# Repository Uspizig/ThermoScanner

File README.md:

# ThermoScanner: The Programmable Scanner for your K-Type Thermo Sensors with Display and Audio

## Features:

1. **AudioAmplifier MAX98357**: Listen to your favourite Tunes with an Audio Amplifier

2. **7 or 8 x K - Type Connectors** Perfect for measuring your heating system

3. **Max31855 or Max31856 Thermo Sensors** High precision

4. **I2C Connector for Sensor**: Connect your favourite I2C Sensor board with the embedded 2.54mm connector

5. **MicroSD Card**: Perfect for storing your thermo logger Data

6. **Wireless Control**: Untehther your development process with the wireless capabilities. With WiFi and BLE, this tool allows remote control and data logging. Users can adjust settings and monitor data from a distance, offering a more flexible development experience.

7. **Open Source & Programmable**: As an open-source device, the Device offers unmatched versatility. It is fully programmable, allowing you to tailor its functionality to your specific applications. This customization extends to software and hardware, opening up endless possibilities for creative and efficient project development.

8. **Compact Design**: Designed for convenience, the Thermologger Board compact and sleek form factor allows for seamless integration into existing setups. Its compatibility with USB PD sources and inline integration capability minimizes the need for additional equipment or extensive redesign, making it a versatile and user-friendly addition to any development environment.

9. **Display**: Monitor live the current status of all Thermo Logger sources or I2C Sensors

10. **Jog Dial** for operating the Device

9. **RGB LED**: Status LED
## Specifications

### Key Features:

### Future Developments:
1. Home Assistant integration

2. Eink Display for Power Saving

## Testing for Performance

At the heart of ThermoLogger's design is a commitment to reliability and performance. To ensure that SenseLoRaCam stands up to real-world demands, we subjected it to testing under use conditions.

## License

MIT License

Copyright (c) 2025 blue2monster

Permission is hereby granted, free of charge, to any person obtaining a copy
of this software and associated documentation files (the "Software"), to deal
in the Software without restriction, including without limitation the rights
to use, copy, modify, merge, publish, distribute, sublicense, and/or sell
copies of the Software, and to permit persons to whom the Software is
furnished to do so, subject to the following conditions:

The above copyright notice and this permission notice shall be included in all
copies or substantial portions of the Software.

THE SOFTWARE IS PROVIDED "AS IS", WITHOUT WARRANTY OF ANY KIND, EXPRESS OR
IMPLIED, INCLUDING BUT NOT LIMITED TO THE WARRANTIES OF MERCHANTABILITY,
FITNESS FOR A PARTICULAR PURPOSE AND NONINFRINGEMENT. IN NO EVENT SHALL THE
AUTHORS OR COPYRIGHT HOLDERS BE LIABLE FOR ANY CLAIM, DAMAGES OR OTHER
LIABILITY, WHETHER IN AN ACTION OF CONTRACT, TORT OR OTHERWISE, ARISING FROM,
OUT OF OR IN CONNECTION WITH THE SOFTWARE OR THE USE OR OTHER DEALINGS IN THE
SOFTWARE.

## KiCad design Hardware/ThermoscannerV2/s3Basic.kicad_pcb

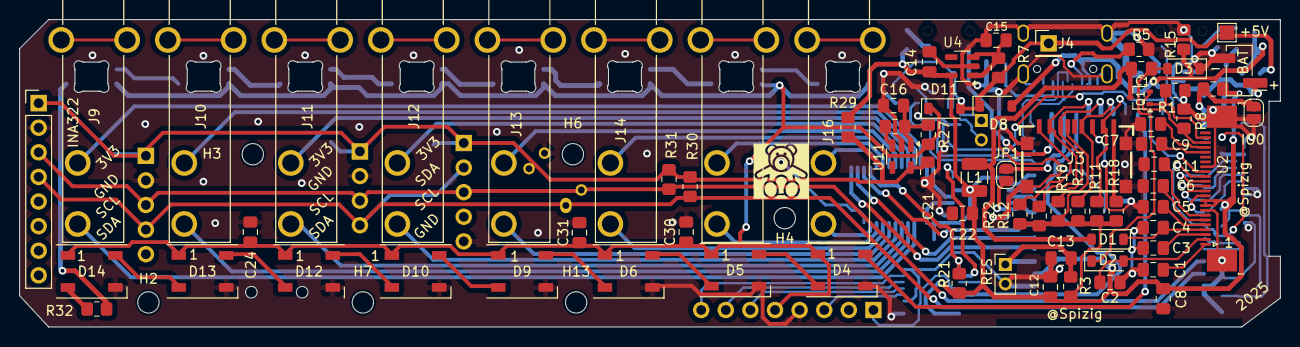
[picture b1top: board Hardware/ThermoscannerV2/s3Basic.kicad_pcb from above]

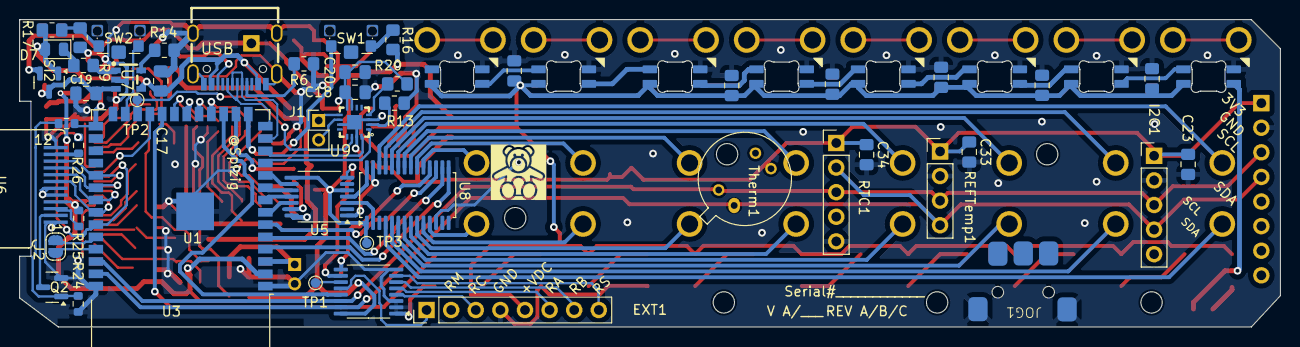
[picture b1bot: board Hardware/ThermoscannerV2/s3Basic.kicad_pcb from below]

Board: 2 copper layers, 130.2 x 31.7 mm, 140 parts (50 on the bottom side), 124 nets.

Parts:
+5V: TestPoint; TestPoint_Pad_1.5x1.5mm
BAT: PWR; PinHeader_1x02_P2.54mm_Vertical_SMD_Pin1Left
C1, C2, C3, C4, C5, C6, C7, C9, C11: 105; C_0805_2012Metric_Pad1.18x1.45mm_HandSolder
C8: 104; C_0805_2012Metric_Pad1.18x1.45mm_HandSolder
C10, C12, C14, C15, C16, C21: 4.7uF50V; C_0805_2012Metric_Pad1.18x1.45mm_HandSolder
C13, C17, C18, C19, C20, C22, C23, C24, C25, C26, C27, C28, C29, C30, C31, C32, C33, C34: 100nF; C_0805_2012Metric_Pad1.18x1.45mm_HandSolder
D1, D2, D3, D8, D11: MBR0530; D_SOD-123
D4, D5, D6, D9, D10, D12, D13, D14: WS2812B; LED_WS2812B_PLCC4_5.0x5.0mm_P3.2mm
D7: LED; LED_0805_2012Metric
D15, D16, D17, D18, D19, D20, D21, D22: SK6812MINI-E; MX_SK6812MINI-E
EXT1: Conn_01x08_Pin; PinHeader_1x08_P2.54mm_Vertical
H2, H3, H4, H6, H7, H13: MountingHole; MountingHole_2.2mm_M2
I2C1: Conn_01x05_Pin; PinHeader_1x05_P2.54mm_Vertical
INA322: Conn_01x08_Pin; PinHeader_1x08_P2.54mm_Vertical
IO0: Conn_01x02_Pin; SolderJumper-2_P1.3mm_Open_RoundedPad1.0x1.5mm
J1: Conn_01x02_Pin; PinHeader_1x02_P2.00mm_Vertical
J2: Conn_01x02_Pin; SolderJumper-2_P1.3mm_Open_RoundedPad1.0x1.5mm
J3: Micro_SD_Card_Det_US; TF-SMD_XKTF-0803-0
J4: Conn_01x01_Pin; PinHeader_1x01_P2.54mm_Vertical
J9, J10, J11, J12, J13, J14, J15, J16: PCC-SMP-V-K; OMEGA_PCC-SMP-V-K
JOG1: jogdial; JogWheel
JP1: SolderJumper_2_Open; SolderJumper-2_P1.3mm_Open_RoundedPad1.0x1.5mm
L1: 68uH1A; L_1210_3225Metric
LOG1, LOG2: MountingHole; baerklein
Q1: Si1308; SOT-323_SC-70
Q2: 2N7002; SOT-23
R1, R3, R4: 10K; R_0805_2012Metric_Pad1.20x1.40mm_HandSolder
R2, R10, R11, R12, R18, R21, R22, R30, R31: 10k; R_0805_2012Metric_Pad1.20x1.40mm_HandSolder
R5, R6: 5k11; R_0805_2012Metric_Pad1.20x1.40mm_HandSolder
R7, R27, R29, R32: 0R; R_0805_2012Metric_Pad1.20x1.40mm_HandSolder
R8: 3R; R_0805_2012Metric_Pad1.20x1.40mm_HandSolder
R9, R14: 1K; R_0805_2012Metric_Pad1.20x1.40mm_HandSolder
R13, R15, R16, R17, R28: 100K; R_0805_2012Metric_Pad1.20x1.40mm_HandSolder
R19: 300K; R_0805_2012Metric_Pad1.20x1.40mm_HandSolder
R20: 330k; R_0805_2012Metric_Pad1.20x1.40mm_HandSolder
R23: 10k; R_0603_1608Metric
R24: 1M; R_0603_1608Metric
R25: 22; R_0603_1608Metric
R26: 0R; R_0603_1608Metric
REFTemp1: Conn_01x04_Pin; PinHeader_1x04_P2.54mm_Vertical
RES: Conn_01x02_Pin; PinHeader_1x02_P2.00mm_Vertical
RTC1: Conn_01x05_Pin; PinHeader_1x05_P2.54mm_Vertical
SI2: SI2301CDS; SOT-23
SW1, SW2: SW_Push; SW_SPST_CK_KMS2xxGP
TP1, TP2, TP3: TestPoint; TestPoint_Pad_D1.0mm
Therm1: MLX90640
U1: ESP32-S3-WROOM-1-Espressif; ESP32-S3-WROOM-1
U2: FPCConn; TE_2-1734839-4_1x24-1MP_P0.5mm_Horizontal
U3: TCA9554PW; TSSOP-16_4.4x5mm_P0.65mm
U4, U11: RT9013; SOT-23-5
U5: MAX31856; TSSOP-14_4.4x5mm_P0.65mm
U6: GC9A01_IPS_display; GC9A01_IPS_display_reversed
U7: TP4065; SOT-23-5_L3.0-W1.7-P0.95-LS2.8-BR
U8: ADG1607xCP; TSSOP-28_4.4x9.7mm_P0.65mm
U9: TQFN-16_L3.0-W3.0-P0.50-BL-EP1.5
USB: KoreanHropartsElecTYPE-C-31-M-12; USB-C_SMD-TYPE-C-31-M-12

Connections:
+3.3VA: C21.2, C23.1, C33.1, C34.1, I2C1.1, INA322.1, R29.1, R30.2, R31.2, REFTemp1.1, RTC1.1, Therm1.2 (VDD), U11.5 (VOUT)
+3.3VP: C8.2, C12.2, C14.2, C22.2, J3.4 (VDD), L1.2, R2.1, R3.2, R4.2, R10.1, R11.2, R12.1, R16.1, R18.2, R21.2, R22.1, R25.2, R29.2, TP3.1, U1.2 (3V3), U2.9 (16), U2.10 (15), U3.16 (VDD), U4.5 (VOUT), U5.5 (AVDD), U5.8 (DVDD), U6.4 (VDD), U8.1 (V_{DD})
+4V: C24.1, C25.1, C26.1, C27.1, C28.1, C29.1, C30.1, C31.1, C32.1, D4.1 (VDD), D5.1 (VDD), D6.1 (VDD), D9.1 (VDD), D10.1 (VDD), D11.1 (K), D12.1 (VDD), D13.1 (VDD), D14.1 (VDD), D15.1 (VDD), D16.1 (VDD), D17.1 (VDD), D18.1 (VDD), D19.1 (VDD), D20.1 (VDD), D21.1 (VDD), D22.1 (VDD), EXT1.5, R27.2
+5V: C15.2, R7.1, U4.1 (VIN), U4.3 (EN)
+5VD: C17.1, D7.2 (A), D8.2 (A), R15.1, R17.1, SI2.1 (G), U7.4 (VCC), USB.A4 (VBUS), USB.A9 (VBUS), USB.B4 (VBUS), USB.B9 (VBUS)
+BATT: BAT.1, C19.2, SI2.3 (D), U7.3 (BAT)
/Audio_BCLK: U1.12 (GPIO8/TOUCH8/ADC1_CH7/SUBSPICS1), U9.16 (BCLK)
/Audio_DIN: U1.11 (GPIO18/U1RXD/ADC2_CH7/CLK_OUT3), U9.1 (DIN)
/Audio_LRC: TP2.1, U1.24 (GPIO47/SPICLK_P/SUBSPICLK_P_DIFF), U9.14 (LRCLK)
/BLK: IO0.1, R4.1, R23.2, U1.27 (GPIO0/BOOT)
/Button1: SW2.1, U1.25 (GPIO48/SPICLK_N/SUBSPICLK_N_DIFF)
/Button2: SW1.2, U1.15 (GPIO3/TOUCH3/ADC1_CH2)
/CMD: J3.3 (CMD), R10.2, U1.19 (GPIO11/TOUCH11/ADC2_CH0/FSPICS0/FSPIIO4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)
/D+: U1.14 (GPIO20/U1CTS/ADC2_CH9/CLK_OUT1/USB_D+), USB.A6 (DP1), USB.B6 (DP2)
/D-: U1.13 (GPIO19/U1RTS/ADC2_CH8/CLK_OUT2/USB_D-), USB.A7 (DN1), USB.B7 (DN2)
/DAT0: J3.7 (DAT0), R11.1, U1.21 (GPIO13/TOUCH13/ADC2_CH2/FSPIQ/FSPIIO7/S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)
/DAT1: J3.8 (DAT1), R18.1
/DAT3: J3.2 (DAT3/CD), R12.2, U1.18 (GPIO10/TOUCH10/ADC1_CH9/FSPICS0/FSPIIO4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)
/DIS_RES: R26.2, U1.35 (MTMS/GPIO42), U2.15 (10)
/EPD_BUSY: U1.23 (GPIO21), U2.16 (9)
/EPD_CLK: U1.33 (MTDO/GPIO40/CLK_OUT2), U2.12 (13), U6.8 (~CS)
/EPD_CS: U1.32 (MTCK/GPIO39/CLK_OUT3/SUBSPICS1), U2.13 (12), U6.9 (SCK)
/EPD_DC: U1.31 (GPIO38/FSPIWP/SUBSPIWP), U2.14 (11), U6.10 (SDI)
/EPD_MOSI: U1.34 (MTDI/GPIO41/CLK_OUT1), U2.11 (14), U6.7 (D/C)
/GPIO_INT: U1.17 (GPIO9/TOUCH9/ADC1_CH8/FSPIHD/SUBSPIHD), U3.13 (~INT)
/LEDK: Q2.3 (D), U6.2 (LEDK)
/ROT_A: EXT1.6, JOG1.1, U3.5 (P1)
/ROT_B: EXT1.7, JOG1.3, U3.6 (P2)
/ROT_C: EXT1.3, U3.4 (P0)
/ROT_L: EXT1.2, I2C1.5, TP1.1, U3.11 (P6)
/ROT_M: EXT1.1, U3.12 (P7)
/ROT_S: EXT1.8, JOG1.2, U3.7 (P3)
/RXD: J2.2, U1.36 (U0RXD/GPIO44/CLK_OUT2)
/SCL: I2C1.3, INA322.3, R31.1, REFTemp1.3, RTC1.3, Therm1.4 (SCL), U1.38 (GPIO2/TOUCH2/ADC1_CH1), U3.14 (SCL)
/SDA: I2C1.4, INA322.4, R30.1, REFTemp1.4, RTC1.2, Therm1.1 (SDA), U1.39 (GPIO1/TOUCH1/ADC1_CH0), U3.15 (SDA)
/SDCK: J3.5 (CLK), R2.2, U1.20 (GPIO12/TOUCH11/ADC2_CH0/FSPICS0/FSPIIO4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)
/SEL_R: Q1.2 (S), R8.2, U2.22 (3)
/T+: U5.4 (T+), U8.28 (DA)
/T+1: J16.P (POS), U8.19 (S1A)
/T+2: J15.P (POS), U8.20 (S2A)
/T+3: J14.P (POS), U8.21 (S3A)
/T+4: J13.P (POS), U8.22 (S4A)
/T+5: J12.P (POS), U8.23 (S5A)
/T+6: J11.P (POS), U8.24 (S6A)
/T+7: J10.P (POS), U8.25 (S7A)
/T+8: J9.P (POS), U8.26 (S8A)
/T-: U5.3 (T-), U8.2 (DB)
/T-1: J16.N (NEG), U8.11 (S1B)
/T-2: J15.N (NEG), U8.10 (S2B)
/T-3: J14.N (NEG), U8.9 (S3B)
/T-4: J13.N (NEG), U8.8 (S4B)
/T-5: J12.N (NEG), U8.7 (S5B)
/T-6: J11.N (NEG), U8.6 (S6B)
/T-7: J10.N (NEG), U8.5 (S7B)
/T-8: J9.N (NEG), U8.4 (S8B)
/TXD: J2.1, U1.37 (U0TXD/GPIO43/CLK_OUT1)
/Thermo_CS5: U1.10 (GPIO17/U1TXD/ADC2_CH6), U5.9 (~CS)
/Thermo_Enable: R21.1, U3.9 (P4), U8.18 (EN)
/Thermo_Fault: JP1.2 (B), U5.13 (~FAULT)
/Thermo_Matrix1: U1.6 (GPIO6/TOUCH6/ADC1_CH5), U8.17 (A0)
/Thermo_Matrix2: U1.5 (GPIO5/TOUCH5/ADC1_CH4), U8.16 (A1)
/Thermo_Matrix3: U1.4 (GPIO4/TOUCH4/ADC1_CH3), U8.15 (A2)
/Thermo_RDY: U3.10 (P5), U5.7 (~DRDY)
/Thermo_SCK: U1.9 (GPIO16/U0CTS/ADC2_CH5/XTAL_32K_NH5), U5.10 (SCK)
/Thermo_SI: U1.7 (GPIO7/TOUCH7/ADC1_CH6), U5.12 (SDI)
/Thermo_SO: U1.8 (GPIO15/U0RTS/ADC2_CH4/XTAL_32K_P), U5.11 (SDO)
/WS2812: D4.4 (DIN), U1.22 (GPIO14/TOUCH14/ADC2_CH3/FSPIWP/FSPIDQS/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)
/WS2812OUT: D14.2 (DOUT), R32.1
GND: BAT.2, C1.1, C2.1, C3.1, C4.1, C5.1, C6.1, C7.1, C8.1, C9.1, C11.1, C12.1, C13.1, C14.1, C15.1, C16.1, C17.2, C18.2, C19.1, C20.2, C21.1, C22.1, C23.2, C24.2, C25.2, C26.2, C27.2, C28.2, C29.2, C30.2, C31.2, C32.2, C33.2, C34.2, D3.1 (K), D4.3 (VSS), D5.3 (VSS), D6.3 (VSS), D9.3 (VSS), D10.3 (VSS), D12.3 (VSS), D13.3 (VSS), D14.3 (VSS), D15.3 (VSS), D16.3 (VSS), D17.3 (VSS), D18.3 (VSS), D19.3 (VSS), D20.3 (VSS), D21.3 (VSS), D22.3 (VSS), EXT1.4, I2C1.2, INA322.2, IO0.2, J3.6 (VSS), J3.10 (SHELL), J3.11 (SHELL), J3.12 (SHELL), J3.13 (SHELL), JOG1.4, Q2.2 (S), R1.2, R5.1, R6.1, R8.1, R13.1, R14.2, R15.2, R19.1, R24.1, REFTemp1.2, RES.2, RTC1.5, Therm1.3 (GND), U1.1 (GND), U1.40 (GND), U1.41 (GND), U2.8 (17), U2.17 (8), U2.MP (25), U3.1 (A0), U3.2 (A1), U3.3 (A2), U3.8 (GND), U4.2 (GND), U5.1 (AGND), U5.14 (DGND), U6.1 (GND), U6.5 (GND), U6.6 (GND), U6.12 (GND), U7.2 (GND), U8.12 (GND), U8.27 (V_{SS}), U9.3 (GND), U9.11 (GND), U9.15 (GND), U9.17 (GND), U11.2 (GND), USB.0, USB.A1 (GND), USB.A12 (GND), USB.B1 (GND), USB.B12 (GND)
unnamed: C10.1, D1.2 (A), L1.1, Q1.3 (D)
unnamed: C4.2, D1.1 (K), U2.4 (21)
unnamed: C2.2, D2.2 (A), U2.2 (23)
unnamed: C10.2, D2.1 (K), D3.2 (A)
unnamed: D4.2 (DOUT), D5.4 (DIN)
unnamed: D5.2 (DOUT), D6.4 (DIN)
unnamed: D6.2 (DOUT), D9.4 (DIN)
unnamed: D7.1 (K), R9.1
unnamed: D9.2 (DOUT), D10.4 (DIN)
unnamed: D10.2 (DOUT), D12.4 (DIN)
unnamed: D12.2 (DOUT), D13.4 (DIN)
unnamed: D13.2 (DOUT), D14.4 (DIN)
unnamed: D15.4 (DIN), R32.2
unnamed: D15.2 (DOUT), D16.4 (DIN)
unnamed: D16.2 (DOUT), D17.4 (DIN)
unnamed: D17.2 (DOUT), D18.4 (DIN)
unnamed: D18.2 (DOUT), D19.4 (DIN)
unnamed: D19.2 (DOUT), D20.4 (DIN)
unnamed: D20.2 (DOUT), D21.4 (DIN)
unnamed: D21.2 (DOUT), D22.4 (DIN)
unnamed: J1.1, U9.9 (OUTP)
unnamed: J1.2, U9.10 (OUTN)
unnamed: J3.1 (DAT2), R22.2
unnamed: J9.SH1 (SHIELD), J9.SH2 (SHIELD)
unnamed: J10.SH1 (SHIELD), J10.SH2 (SHIELD)
unnamed: J11.SH1 (SHIELD), J11.SH2 (SHIELD)
unnamed: J12.SH1 (SHIELD), J12.SH2 (SHIELD)
unnamed: J13.SH1 (SHIELD), J13.SH2 (SHIELD)
unnamed: J14.SH1 (SHIELD), J14.SH2 (SHIELD)
unnamed: J15.SH1 (SHIELD), J15.SH2 (SHIELD)
unnamed: J16.SH1 (SHIELD), J16.SH2 (SHIELD)
unnamed: JP1.1 (A), U1.16 (GPIO46)
unnamed: Q1.1 (G), R1.1, U2.23 (2)
unnamed: Q2.1 (G), R23.1, R24.2
unnamed: R16.2, SW1.1
unnamed: R17.2, R19.2, SW2.2
unnamed: C13.2, R3.1, RES.1, U1.3 (EN)
unnamed: C7.2, U2.21 (4)
unnamed: C9.2, U2.20 (5)
unnamed: C11.2, U2.7 (18)
unnamed: C6.2, U2.6 (19)
unnamed: C5.2, U2.5 (20)
unnamed: C3.2, U2.3 (22)
unnamed: C1.2, U2.1 (24)
unnamed: R25.1, U6.3 (LEDA)
unnamed: R26.1, U6.11 (~RESET)
unnamed: R9.2, U7.1 (CHRG)
unnamed: R14.1, U7.5 (PROG)
unnamed: R13.2, U9.2 (GAIN)
unnamed: R20.2, U9.4 (SD)
unnamed: R28.1, U11.3 (EN)
unnamed: C16.2, R27.1, R28.2, U11.1 (VIN)
unnamed: R6.2, USB.A5 (CC1)
unnamed: R5.2, USB.B5 (CC2)
VDC: +5V.1, C18.1, C20.1, D8.1 (K), D11.2 (A), J4.1, R7.2, R20.1, SI2.2 (S), U9.7 (VDD), U9.8 (VDD)

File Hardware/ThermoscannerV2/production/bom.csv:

Designator,Footprint,Quantity,Value,LCSC Part #
+5V,TestPoint_Pad_1.5x1.5mm,1,TestPoint,
BAT,PinHeader_1x02_P2.54mm_Vertical_SMD_Pin1Left,1,PWR,
"C1, C11, C2, C3, C4, C5, C6, C7, C9",0805,9,105,
"C10, C12, C14, C15, C16, C21",0805,6,4.7uF50V,
"C13, C17, C18, C19, C20, C22, C23, C24, C25, C26, C27, C28, C29, C30, C31, C32, C33, C34",0805,18,100nF,
C8,0805,1,104,
"D1, D11, D2, D3, D8",D_SOD-123,5,MBR0530,
"D10, D12, D13, D14, D4, D5, D6, D9",LED_WS2812B_PLCC4_5.0x5.0mm_P3.2mm,8,WS2812B,
"D15, D16, D17, D18, D19, D20, D21, D22",MX_SK6812MINI-E,8,SK6812MINI-E,
D7,0805,1,LED,
"EXT1, INA322",PinHeader_1x08_P2.54mm_Vertical,2,Conn_01x08_Pin,
"H13, H2, H3, H4, H6, H7",MountingHole_2.2mm_M2,6,MountingHole,
"I2C1, RTC1",PinHeader_1x05_P2.54mm_Vertical,2,Conn_01x05_Pin,
"IO0, J2",SolderJumper-2_P1.3mm_Open_RoundedPad1.0x1.5mm,2,Conn_01x02_Pin,
"J1, RES",PinHeader_1x02_P2.00mm_Vertical,2,Conn_01x02_Pin,
"J10, J11, J12, J13, J14, J15, J16, J9",OMEGA_PCC-SMP-V-K,8,PCC-SMP-V-K,
J3,TF-SMD_XKTF-0803-0,1,Micro_SD_Card_Det_US,
J4,PinHeader_1x01_P2.54mm_Vertical,1,Conn_01x01_Pin,
JOG1,JogWheel,1,jogdial,
L1,1210,1,68uH1A,
Q1,SOT-323_SC-70,1,Si1308,
Q2,SOT-23,1,2N7002,
"R1, R10, R11, R12, R18, R2, R21, R22, R3, R30, R31, R4",0805,12,10K,
"R13, R15, R16, R17, R28",0805,5,100K,
"R14, R9",0805,2,1K,
R19,0805,1,300K,
R20,0805,1,330k,
R23,0603,1,10k,
R24,0603,1,1M,
R25,0603,1,22,
R26,0603,1,0R,
"R27, R29, R32, R7",0805,4,0R,
"R5, R6",0805,2,5k11,
R8,0805,1,3R,
REFTemp1,PinHeader_1x04_P2.54mm_Vertical,1,Conn_01x04_Pin,
SI2,SOT-23,1,SI2301CDS,
"SW1, SW2",SW_SPST_CK_KMS2xxGP,2,SW_Push,
"TP1, TP2, TP3",TestPoint_Pad_D1.0mm,3,TestPoint,
Therm1,MLX90640,1,MLX90640,
U1,ESP32-S3-WROOM-1,1,ESP32-S3-WROOM-1-Espressif,
"U11, U4",SOT-23-5,2,RT9013,
U2,TE_2-1734839-4_1x24-1MP_P0.5mm_Horizontal,1,FPCConn,
U3,TSSOP-16_4.4x5mm_P0.65mm,1,TCA9554PW,
U5,TSSOP-14_4.4x5mm_P0.65mm,1,MAX31856,
U6,GC9A01_IPS_display_reversed,1,GC9A01_IPS_display,
U7,SOT-23-5_L3.0-W1.7-P0.95-LS2.8-BR,1,TP4065,
U8,TSSOP-28_4.4x9.7mm_P0.65mm,1,ADG1607xCP,
U9,TQFN-16_L3.0-W3.0-P0.50-BL-EP1.5,1,~,
USB,USB-C_SMD-TYPE-C-31-M-12,1,KoreanHropartsElecTYPE-C-31-M-12,

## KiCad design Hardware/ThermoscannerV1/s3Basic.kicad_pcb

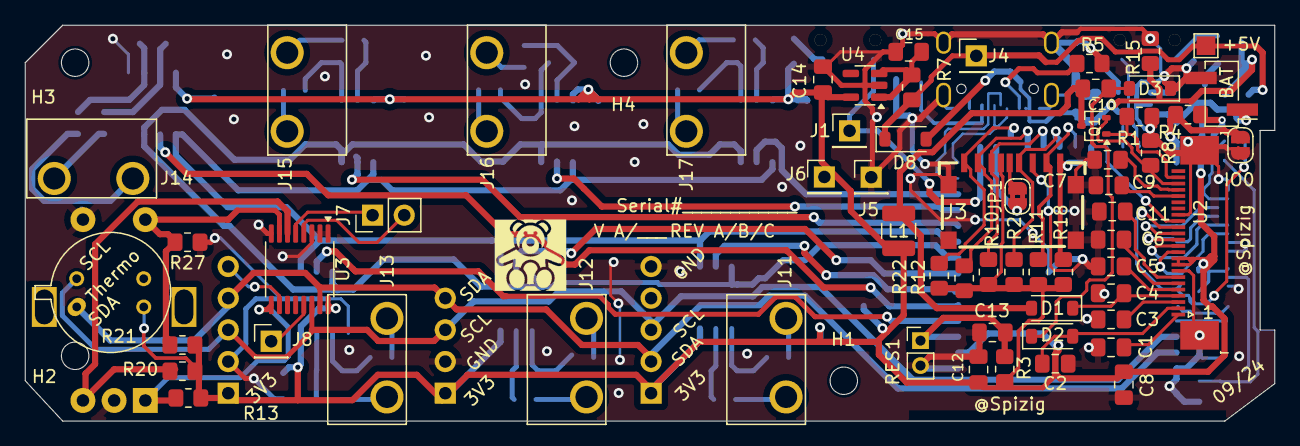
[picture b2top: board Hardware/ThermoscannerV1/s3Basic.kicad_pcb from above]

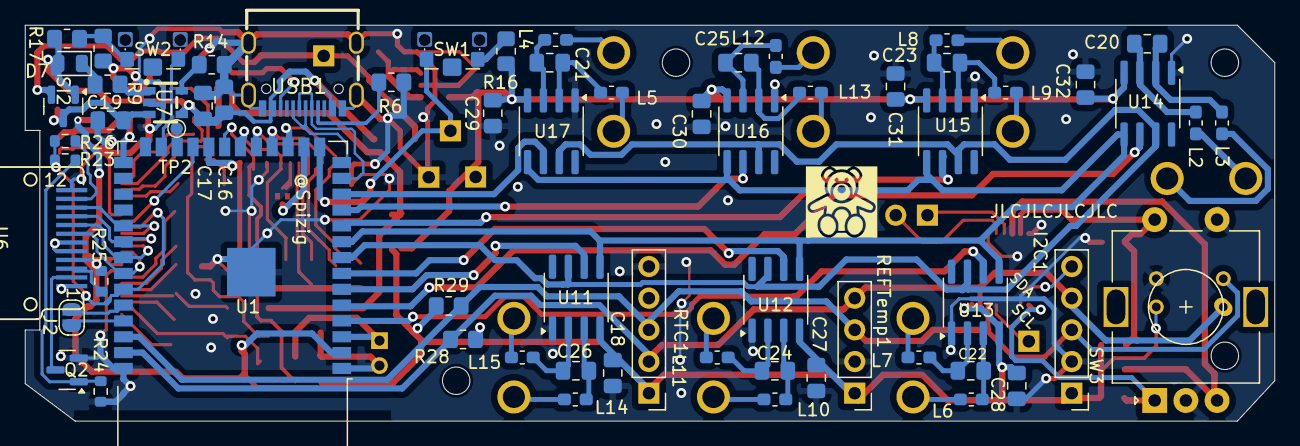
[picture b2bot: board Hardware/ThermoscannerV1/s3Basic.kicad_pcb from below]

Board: 2 copper layers, 100.2 x 31.7 mm, 132 parts (66 on the bottom side), 99 nets.

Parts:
+5V: TestPoint; TestPoint_Pad_1.5x1.5mm
BAT: PWR; PinHeader_1x02_P2.54mm_Vertical_SMD_Pin1Left
C1, C2, C3, C4, C5, C6, C7, C9, C11: 105; C_0805_2012Metric_Pad1.18x1.45mm_HandSolder
C8: 104; C_0805_2012Metric_Pad1.18x1.45mm_HandSolder
C10, C12, C14, C15: 4.7uF50V; C_0805_2012Metric_Pad1.18x1.45mm_HandSolder
C13, C17, C18, C19, C20, C21, C22, C23, C24, C25, C26, C27, C28, C29, C30, C31, C32: 100nF; C_0805_2012Metric_Pad1.18x1.45mm_HandSolder
C16: 1uF; C_0805_2012Metric_Pad1.18x1.45mm_HandSolder
D1, D2, D3, D8: MBR0530; D_SOD-123
D7: LED; LED_0805_2012Metric
H1, H2, H3, H4: MountingHole; MountingHole_2.2mm_M2
I2C1: Conn_01x05_Pin; PinHeader_1x05_P2.54mm_Vertical
IO0: Conn_01x02_Pin; SolderJumper-2_P1.3mm_Open_RoundedPad1.0x1.5mm
J1, J4, J5, J6, J8: Conn_01x01_Pin; PinHeader_1x01_P2.54mm_Vertical
J2: Conn_01x02_Pin; SolderJumper-2_P1.3mm_Open_RoundedPad1.0x1.5mm
J3: Micro_SD_Card_Det_US; TF-SMD_XKTF-0803-0
J7: Conn_01x02_Pin; PinHeader_1x02_P2.54mm_Vertical
J11, J12, J13, J14, J15, J16, J17: PCC-SMP-V-K; OMEGA_PCC-SMP-V-K
JP1: Jumper_2_Open; SolderJumper-2_P1.3mm_Bridged2Bar_RoundedPad1.0x1.5mm
L1: 68uH1A; L_1210_3225Metric
L2, L3, L4, L5, L6, L7, L8, L9, L10, L11, L12, L13, L14, L15: L; L_0603_1608Metric_Pad1.05x0.95mm_HandSolder
LOG1, LOG2: MountingHole; baerklein
Q1: Si1308; SOT-323_SC-70
Q2: 2N7002; SOT-23
R1, R3, R4: 10K; R_0805_2012Metric_Pad1.20x1.40mm_HandSolder
R2, R10, R11, R12, R13, R18, R20, R21, R22, R27, R28, R29: 10k; R_0805_2012Metric_Pad1.20x1.40mm_HandSolder
R5, R6: 5k11; R_0805_2012Metric_Pad1.20x1.40mm_HandSolder
R7: 0R; R_0805_2012Metric_Pad1.20x1.40mm_HandSolder
R8: 3R; R_0805_2012Metric_Pad1.20x1.40mm_HandSolder
R9, R14: 1K; R_0805_2012Metric_Pad1.20x1.40mm_HandSolder
R15, R16, R17: 100K; R_0805_2012Metric_Pad1.20x1.40mm_HandSolder
R19: 300K; R_0805_2012Metric_Pad1.20x1.40mm_HandSolder
R23: 10k; R_0603_1608Metric
R24: 1M; R_0603_1608Metric
R25: 22; R_0603_1608Metric
R26: 0R; R_0603_1608Metric
REFTemp1: Conn_01x04_Pin; PinHeader_1x04_P2.54mm_Vertical
RES1: Conn_01x02_Pin; PinHeader_1x02_P2.00mm_Vertical
RTC1: Conn_01x05_Pin; PinHeader_1x05_P2.54mm_Vertical
SI2: SI2301CDS; SOT-23
SW1, SW2: SW_Push; SW_SPST_CK_KMS2xxGP
SW3: Rotary_Encoder_Switch; RotaryEncoder_Alps_EC11E-Switch_Vertical_H20mm
TP2: TestPoint; TestPoint_Pad_D1.0mm
Thermo: MLX90640
U1: ESP32-S3-WROOM-1-Espressif; ESP32-S3-WROOM-1
U2: FPCConn; TE_2-1734839-4_1x24-1MP_P0.5mm_Horizontal
U3: TCA9554PW; TSSOP-16_4.4x5mm_P0.65mm
U4: RT9013; SOT-23-5
U6: GC9A01_IPS_display; GC9A01_IPS_display_reversed
U7: TP4065; SOT-23-5_L3.0-W1.7-P0.95-LS2.8-BR
U11, U12, U13, U14, U15, U16, U17: MAX31855KASA; SOIC-8_3.9x4.9mm_P1.27mm
USB1: KoreanHropartsElecTYPE-C-31-M-12; USB-C_SMD-TYPE-C-31-M-12

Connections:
+3.3VP: C8.2, C12.2, C14.2, C18.2, C27.2, C28.2, C29.2, C30.2, C31.2, C32.2, I2C1.1, J3.4 (VDD), J6.1, L1.2, R2.1, R3.2, R4.2, R10.1, R11.2, R12.1, R13.1, R16.1, R18.2, R20.2, R21.2, R22.1, R25.2, R28.2, R29.2, REFTemp1.1, RTC1.1, Thermo.2 (VDD), U1.2 (3V3), U2.9 (16), U2.10 (15), U3.16 (VDD), U4.5 (VOUT), U6.4 (VDD), U11.4 (V_CC), U12.4 (V_CC), U13.4 (V_CC), U14.4 (V_CC), U15.4 (V_CC), U16.4 (V_CC), U17.4 (V_CC)
+5V: C15.2, R7.1, U4.1 (VIN), U4.3 (EN)
+5VD: C16.1, C17.1, D7.2 (A), D8.2 (A), R15.1, R17.1, SI2.1 (G), U7.4 (VCC), USB1.A4 (VBUS), USB1.A9 (VBUS), USB1.B4 (VBUS), USB1.B9 (VBUS)
+BATT: BAT.1, C19.2, SI2.3 (D), U7.3 (BAT)
/BLK: R23.2, R26.2, U1.35 (MTMS/GPIO42), U2.15 (10)
/Button1: SW2.1, U1.25 (GPIO48/SPICLK_N/SUBSPICLK_N_DIFF)
/Button2: J1.1, SW1.2, U1.15 (GPIO3/TOUCH3/ADC1_CH2)
/CMD: J3.3 (CMD), R10.2, U1.19 (GPIO11/TOUCH11/ADC2_CH0/FSPICS0/FSPIIO4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)
/D+: U1.14 (GPIO20/U1CTS/ADC2_CH9/CLK_OUT1/USB_D+), USB1.A6 (DP1), USB1.B6 (DP2)
/D-: U1.13 (GPIO19/U1RTS/ADC2_CH8/CLK_OUT2/USB_D-), USB1.A7 (DN1), USB1.B7 (DN2)
/DAT0: J3.7 (DAT0), R11.1, U1.21 (GPIO13/TOUCH13/ADC2_CH2/FSPIQ/FSPIIO7/S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)
/DAT1: J3.8 (DAT1), R18.1, U1.22 (GPIO14/TOUCH14/ADC2_CH3/FSPIWP/FSPIDQS/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)
/DAT2: J3.1 (DAT2), R22.2, U1.17 (GPIO9/TOUCH9/ADC1_CH8/FSPIHD/SUBSPIHD)
/DAT3: J3.2 (DAT3/CD), R12.2, U1.18 (GPIO10/TOUCH10/ADC1_CH9/FSPICS0/FSPIIO4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)
/EPD_BUSY: U1.23 (GPIO21), U2.16 (9)
/EPD_CLK: U1.33 (MTDO/GPIO40/CLK_OUT2), U2.12 (13), U6.8 (~CS)
/EPD_CS: U1.32 (MTCK/GPIO39/CLK_OUT3/SUBSPICS1), U2.13 (12), U6.9 (SCK)
/EPD_DC: U1.31 (GPIO38/FSPIWP/SUBSPIWP), U2.14 (11), U6.10 (SDI)
/EPD_MOSI: U1.34 (MTDI/GPIO41/CLK_OUT1), U2.11 (14), U6.7 (D/C)
/IO0: IO0.1, R4.1, U1.27 (GPIO0/BOOT)
/LEDK: Q2.3 (D), U6.2 (LEDK)
/ROT_A: R13.2, SW3.A, U3.9 (P4)
/ROT_B: R20.1, SW3.B, U3.6 (P2)
/ROT_C: J7.2, U3.4 (P0)
/ROT_D: J7.1, U3.5 (P1)
/ROT_I: I2C1.5, U3.10 (P5)
/ROT_S: R21.1, R27.2, SW3.S2, U3.7 (P3)
/RXD: J2.2, U1.36 (U0RXD/GPIO44/CLK_OUT2)
/SCL: I2C1.3, R29.1, REFTemp1.3, RTC1.3, Thermo.4 (SCL), U1.38 (GPIO2/TOUCH2/ADC1_CH1), U3.14 (SCL)
/SDA: I2C1.4, R28.1, REFTemp1.4, RTC1.2, Thermo.1 (SDA), U1.39 (GPIO1/TOUCH1/ADC1_CH0), U3.15 (SDA)
/SDCK: J3.5 (CLK), R2.2, U1.20 (GPIO12/TOUCH11/ADC2_CH0/FSPICS0/FSPIIO4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)
/SD_DETECT: J3.9 (SWITCH), JP1.2 (B)
/SEL_R: Q1.2 (S), R8.2, U2.22 (3)
/TXD: J2.1, U1.37 (U0TXD/GPIO43/CLK_OUT1)
/Thermo_CS1: U1.6 (GPIO6/TOUCH6/ADC1_CH5), U11.6 (~CS)
/Thermo_CS2: U1.7 (GPIO7/TOUCH7/ADC1_CH6), U12.6 (~CS)
/Thermo_CS3: U1.4 (GPIO4/TOUCH4/ADC1_CH3), U13.6 (~CS)
/Thermo_CS4: U1.5 (GPIO5/TOUCH5/ADC1_CH4), U14.6 (~CS)
/Thermo_CS5: U1.10 (GPIO17/U1TXD/ADC2_CH6), U15.6 (~CS)
/Thermo_CS6: U1.11 (GPIO18/U1RXD/ADC2_CH7/CLK_OUT3), U16.6 (~CS)
/Thermo_CS7: U1.12 (GPIO8/TOUCH8/ADC1_CH7/SUBSPICS1), U17.6 (~CS)
/Thermo_SCK: U1.9 (GPIO16/U0CTS/ADC2_CH5/XTAL_32K_NH5), U11.5 (SCK), U12.5 (SCK), U13.5 (SCK), U14.5 (SCK), U15.5 (SCK), U16.5 (SCK), U17.5 (SCK)
/Thermo_SO: U1.8 (GPIO15/U0RTS/ADC2_CH4/XTAL_32K_P), U11.7 (SO), U12.7 (SO), U13.7 (SO), U14.7 (SO), U15.7 (SO), U16.7 (SO), U17.7 (SO)
GND: BAT.2, C1.1, C2.1, C3.1, C4.1, C5.1, C6.1, C7.1, C8.1, C9.1, C11.1, C12.1, C13.1, C14.1, C15.1, C16.2, C17.2, C18.1, C19.1, C27.1, C28.1, C29.1, C30.1, C31.1, C32.1, D3.1 (K), I2C1.2, IO0.2, J3.6 (VSS), J3.10 (SHELL), J3.11 (SHELL), J3.12 (SHELL), J3.13 (SHELL), J5.1, Q2.2 (S), R1.2, R5.1, R6.1, R8.1, R14.2, R15.2, R19.1, R24.1, R27.1, REFTemp1.2, RES1.2, RTC1.5, SW3.C, SW3.S1, Thermo.3 (GND), U1.1 (GND), U1.40 (GND), U1.41 (GND), U2.8 (17), U2.17 (8), U2.MP (26), U3.1 (A0), U3.2 (A1), U3.3 (A2), U3.8 (GND), U4.2 (GND), U6.1 (GND), U6.5 (GND), U6.6 (GND), U6.12 (GND), U7.2 (GND), U11.1 (GND), U12.1 (GND), U13.1 (GND), U14.1 (GND), U15.1 (GND), U16.1 (GND), U17.1 (GND), USB1.0, USB1.A1 (GND), USB1.A12 (GND), USB1.B1 (GND), USB1.B12 (GND)
unnamed: C10.1, D1.2 (A), L1.1, Q1.3 (D)
unnamed: C4.2, D1.1 (K), U2.4 (21)
unnamed: C2.2, D2.2 (A), U2.2 (23)
unnamed: C10.2, D2.1 (K), D3.2 (A)
unnamed: D7.1 (K), R9.1
unnamed: J8.1, U3.13 (~INT)
unnamed: J11.N (NEG), L15.1
unnamed: J11.P (POS), L14.1
unnamed: J12.N (NEG), L11.1
unnamed: J12.P (POS), L10.1
unnamed: J13.N (NEG), L7.1
unnamed: J13.P (POS), L6.1
unnamed: J14.N (NEG), L3.1
unnamed: J14.P (POS), L2.1
unnamed: J15.N (NEG), L9.1
unnamed: J15.P (POS), L8.1
unnamed: J16.N (NEG), L13.1
unnamed: J16.P (POS), L12.1
unnamed: J17.N (NEG), L5.1
unnamed: J17.P (POS), L4.1
unnamed: JP1.1 (A), U1.16 (GPIO46)
unnamed: Q1.1 (G), R1.1, U2.23 (2)
unnamed: Q2.1 (G), R23.1, R24.2
unnamed: R16.2, SW1.1
unnamed: R17.2, R19.2, SW2.2
unnamed: C13.2, R3.1, RES1.1, U1.3 (EN)
unnamed: TP2.1, U1.24 (GPIO47/SPICLK_P/SUBSPICLK_P_DIFF)
unnamed: C7.2, U2.21 (4)
unnamed: C9.2, U2.20 (5)
unnamed: C11.2, U2.7 (18)
unnamed: C6.2, U2.6 (19)
unnamed: C5.2, U2.5 (20)
unnamed: C3.2, U2.3 (22)
unnamed: C1.2, U2.1 (24)
unnamed: R25.1, U6.3 (LEDA)
unnamed: R26.1, U6.11 (~RESET)
unnamed: R9.2, U7.1 (CHRG)
unnamed: R14.1, U7.5 (PROG)
unnamed: C26.1, L14.2, U11.3 (T+)
unnamed: C26.2, L15.2, U11.2 (T-)
unnamed: C24.1, L10.2, U12.3 (T+)
unnamed: C24.2, L11.2, U12.2 (T-)
unnamed: C22.1, L6.2, U13.3 (T+)
unnamed: C22.2, L7.2, U13.2 (T-)
unnamed: C20.1, L2.2, U14.3 (T+)
unnamed: C20.2, L3.2, U14.2 (T-)
unnamed: C23.1, L8.2, U15.3 (T+)
unnamed: C23.2, L9.2, U15.2 (T-)
unnamed: C25.1, L12.2, U16.3 (T+)
unnamed: C25.2, L13.2, U16.2 (T-)
unnamed: C21.1, L4.2, U17.3 (T+)
unnamed: C21.2, L5.2, U17.2 (T-)
unnamed: R6.2, USB1.A5 (CC1)
unnamed: R5.2, USB1.B5 (CC2)
VDC: +5V.1, D8.1 (K), J4.1, R7.2, SI2.2 (S)
